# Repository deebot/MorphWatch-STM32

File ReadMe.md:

# MorphWatch-STM32

# Description
Morph watch is a wearable made for makers and hackers who want to do more with  their devices and want to have control over their data. As a normal functional device it shows time, date and no of steps,weather data . But it is more than that it can be used to run machine learning algorithums on 6 Axis IMU MPU6050 data to detect gestures. The small form factor and integrated battery also allows the user to attach the watch to a target lets say attach it to your bicycle to gather the vibration data, or attach it to a machine to gather the vibration data to  train a model for predicting breakdown and service durations. The device also  provides I2C interface to attach more sensorS as modules. It also provides interface  to connect with  STLINK-V2 and supports full debugging features using breakpoints and print statements. The watch is intended to have 2 Modes:

- Ultra Low Power Mode : In this mode the L476RG controller  wakes up ever 1 minute to update the minutes and then sleeps. The 2 buttons are configures as external intruppts and can be pressed to wake up the controller and do other tasks like going though the Menu and getting the status of external senors or IMU data. This mode should give very long battery life

- Normal Mode: In this mode the microcontroller is active all the time and can count steps and perform machine learning algorithums.

## <u>Features supported by Hardware</u>
Morph Watch has STM32-L476RG at its heart which has 128KB SRAM and 1MB Flash suitable for running Edge AI models. It has internal RTC and DFU support which allows updating the firmware over USB without any external USB to Serial convertor or Programmer. The watch has 2 buttons to navigate menu or work as external interrupts. The battary can be charegd using the onboard charging IC.The battery status can be monitored and diplayed on the Eink display. A 9 Axis IMU is onboard which allows user to create innovative projects. A vibration moter can be connected to get vibration feedback. A Bluetooth module JDY08 based on TI's CC2541 Chip allows user to connect to Android device over bluetooth 4.0. Diagram Below shoews the board and placement of  key components.

## <u>Schematic</u>

## <u>Uploading Code and Debugging</u>
Uploading the code is possible though USB in DFU mode by connecting the Boot Pin to HIGH  by either connecting the jumper using external wire or by shorting the jumper JP1 by soldering. To exit the DFU mode remove the jumper JP1 and powercycle. The code can also be uploaded using the Serial Wire debug interface. STlink Debugger/Programmer is need to use this interface.

## TO DO list

### Phase 1:

- [ ] Implement code to interface EINK Display using SPI protocol and control partial and complete refresh
- [ ] Implement code to interface IMU using I2C protocol and grab the raw data.
- [ ] Understanding the internal RTC functionality of L476RG and implementing code to get time and data.
- [ ] Understanding intruppts on L476RG and configuring buttons as external intruppts
- [ ] Implementing code to control the vibration motor

### Phase 2:

- [ ] Creating Menus on the Eink Display and switching between menu using buttons.
- [ ] Recognising Gestures using IMU and exploring Kalman filter 
- [ ] Understanding CRC hardware on board and implementing code to grab data. This functionality will be used to send CRC along with data to detect tempering
- [ ] Figure out a Generic app to check the functionality
- [ ] Integration of all the features to achieve functional Watch

### Phase 3:

- [ ] Understanding the Bluetooth4.0 and Write code to interface Bluetooth in transparent mode using UART
- [ ] Integration of Bluetooth functionality with other features
- [ ] Using  Bosch'S BlechC using STM HAL code.
- [ ] Exploring Low power modes of L476RG

## Story Behind : 
### A little story telling:

  Morph watch is inpired by [Watchy|SQFMI ](https://www.crowdsupply.com/sqfmi/watchy) which you can also back on crowdsource as on today 1Feb2021. For a long time i wanted to build my own smart watch which is hackable. My idea was to have a development board which is also a product in itself with certain concrete functionality and that is why i narrowed down on having a watch because i can have it on me as a watch but it can also be something else, a learning tool and its functionality can be extended by adding mods to it. 
### Why I chose what i chose
  I chose to build Morph Watch on STM32 L476RG which is based on ARM cortex M4. I have  some sort of romatisim for ARM architecture and  its not long since i have shifted from 8 bit segment to more capable 32 bit controllers which i often see in tear down of professional products, infact the Pebble watch was based on a STM32 microntroller and TI's bluetooth chip. Also because i had a nucleo board and already had a JDY08 module to write software. Further this STM variaent is quite capable of running AI algos and also also supports various low power modes. Further with  the STM line  it would be very easy to incorporate wirless line like STM32wb to add different wifi technologies to this watch. While ESP32 with Arduino IDE are very easy to use but I now prefer more serious debugging techniques using Debugger and breakpoints which is supported on this board.
  Also read  [MORPH watch Hackaday ](https://hackaday.io/project/177315-morph-watch)

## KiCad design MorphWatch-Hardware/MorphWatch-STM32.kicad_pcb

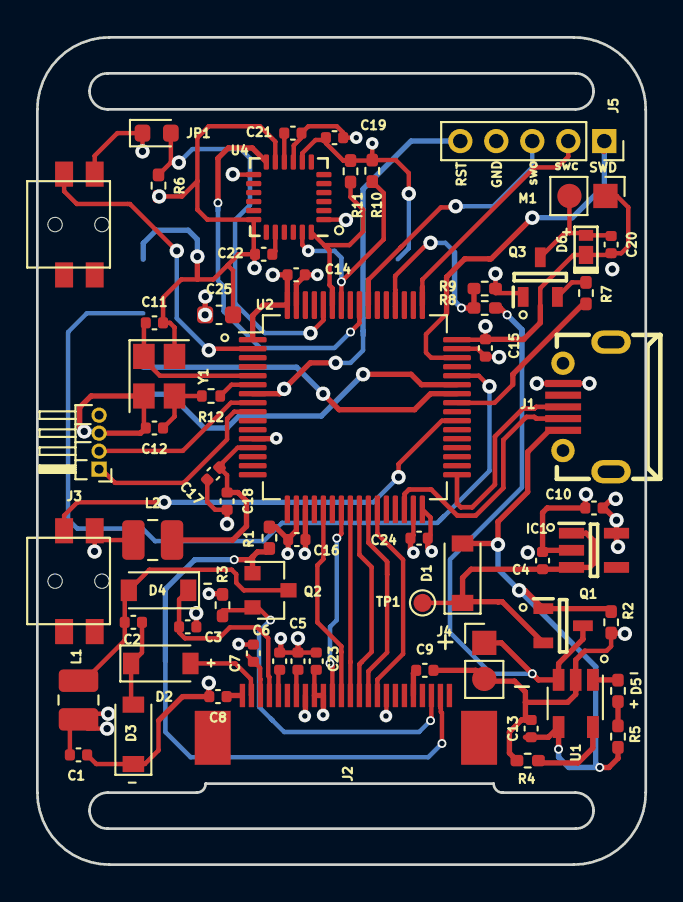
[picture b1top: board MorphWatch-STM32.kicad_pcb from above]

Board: 4 copper layers, 33.8 x 46.0 mm, 64 parts (1 on the bottom side), 52 nets.

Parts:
C1: 4.7uF/50v; C_0402_1005Metric
C2, C10: 4.7uf/50v; C_0402_1005Metric
C3, C5, C6, C7, C8, C9, C23: 1uf/50v; C_0402_1005Metric
C4, C13: 1uf; C_0402_1005Metric
C11, C12, C14, C15, C16, C17, C18, C19, C20, C21, C22, C24: C; C_0402_1005Metric
C25: 4.7uf; C_0603_1608Metric
D1, D2, D3, D4: MBR0530; D_SOD-123
D5: LED; R_0402_1005Metric_Pad0.72x0.64mm_HandSolder
D6: Diode; U-DFN1608-2_L1.6-W0.8-RD
IC1: ME6211C33M5G-N; SOT95P270X145-5N
J1: USB; MICRO-USB-SMD_MICROXNJ
J2: Conn_01x24; 24_Pins_0.5mm_Pitch_ZIF_Connector_UP
J3: Conn_01x04; PinHeader_1x04_P1.00mm_Horizontal
J4: Conn_01x02; Motor_Header
J5: Conn_01x05; PinSocket_1x05_P2.00mm_Vertical
JP1: SolderJumper_2_Open; D_0603_1608Metric
L1: 27uH; L_1008_2520Metric
L2: 27n; L_1008_2520Metric
M1: Motor_DC_ALT; Motor_Header
Q1: CJ2301_S1; SOT95P240X115-3N
Q2: DMN3042L; SOT-23
Q3: S8050; SOT95P240X115-3N
R1, R2, R4: 10k; R_0402_1005Metric_Pad0.72x0.64mm_HandSolder
R3: 3; R_0402_1005Metric_Pad0.72x0.64mm_HandSolder
R5: 1k; R_0402_1005Metric_Pad0.72x0.64mm_HandSolder
R6, R7, R8, R9: R; R_0402_1005Metric_Pad0.72x0.64mm_HandSolder
R10, R11: 2.2k; R_0402_1005Metric_Pad0.72x0.64mm_HandSolder
R12: 5; R_0402_1005Metric
S1, S2: GPTS203211B; K2-1114SA-A4SW-06
TP1: TestPoint; TestPoint_Pad_D1.0mm
U1: TP4054; TSOT-23-5
U2: STM32L476RGTx; LQFP-64_10x10mm_P0.5mm
U3: JDY-08; JDY-08_HandSoldering
U4: MPU-6050; InvenSense_QFN-24_4x4mm_P0.5mm
Y1: Crystal_GND24; Crystal_SMD_3225-4Pin_3.2x2.5mm

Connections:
+3.3VA: C17.1, C18.1, L2.2, U2.13
+3V3: C1.1, C10.1, C14.1, C15.1, C16.1, C19.1, C20.1, C23.2, C24.1, C25.1, D6.1, IC1.5, J2.15, J2.16, J3.4, JP1.1, L1.1, L2.1, M1.1, R10.2, R11.2, S1.2, S2.2, U2.1, U2.19, U2.32, U2.48, U2.64, U3.1, U4.8, U4.13
+BATT: J4.1, Q1.3, R8.1, U1.3
BATT_STAT: R8.2, R9.1, U2.52
BUSY: J2.9, U2.27
BUT1: S1.1, U2.39
BUT2: S2.1, U2.2
DC: J2.11, U2.25
EXTSENSCL: J3.2, U2.8
EXTSENSDA: J3.1, U2.9
GDR: J2.2, Q2.1, R1.2
GND: C1.2, C3.2, C4.2, C5.2, C6.2, C7.2, C8.2, C9.2, C10.2, C11.2, C12.2, C13.1, C14.2, C15.2, C16.2, C17.2, C18.2, C19.2, C21.2, C22.2, C23.1, C24.2, C25.2, D3.1, IC1.2, J1.5, J2.8, J2.17, J3.3, J4.2, J5.4, Q3.1, R1.1, R2.1, R3.1, R4.2, R6.2, R9.2, U1.2, U2.12, U2.18, U2.31, U2.47, U2.63, U3.24, U4.1, U4.9, U4.11, U4.18, Y1.2, Y1.4
INT: U2.56, U4.12
MOSI: J2.14, U2.23
NRST: J5.5, U2.7
unnamed: C2.1, D2.1, D3.2
unnamed: C2.2, D4.2, L1.2, Q2.3
unnamed: C4.1, D1.1, IC1.1, IC1.3, Q1.2, TP1.1
unnamed: C5.1, J2.18
unnamed: C6.1, J2.20
unnamed: C7.1, J2.22
unnamed: C8.1, J2.24
unnamed: C9.1, J2.5
unnamed: C11.1, U2.5, Y1.1
unnamed: C12.1, R12.2, Y1.3
unnamed: C20.2, D6.2, M1.2, Q3.3
unnamed: C21.1, U4.10
unnamed: C22.1, U4.20
unnamed: D5.1, U1.1
unnamed: D5.2, R5.2
unnamed: JP1.2, R6.1, U2.60
unnamed: Q3.2, R7.1
unnamed: R4.1, U1.5
unnamed: R12.1, U2.6
PREVGH: C3.1, D4.1, J2.21
PREVGL: D2.2, J2.23
RES: J2.10, U2.26
RESE: J2.3, Q2.2, R3.2
RXD: U2.42, U3.20
SCK: J2.13, U2.21
SS: J2.12, U2.24
SWCLK: J5.2, U2.49
TXD: U2.43, U3.19
TraceSWO: J5.3, U2.55
USB_B+: J1.3, U2.33
USB_B-: J1.2, U2.30
VBUS: C13.2, D1.2, J1.1, Q1.1, R2.2, R5.1, U1.4
VIB_MOT: R7.2, U2.41
Wakeup: U2.44, U3.22
imuSCL: R10.1, U2.58, U4.23
imuSDA: R11.1, U2.59, U4.24
swdebug: J5.1, U2.46

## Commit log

2021-02-02 Added Schematic,BoardFile and associated files
2021-02-02 Added Readme File
2021-02-03 Added Images
2021-02-03 Added information about features, uploading code and displayed images
2021-02-04 Made changes to satisfy DRC
2021-02-04 Added Gerber files and Pick & Place file
2021-02-04 Added tasks in the todo list
2021-02-04 Modified the Board to funlfil DRC rules
2021-02-05 Updated Board to satisfy DRC
2021-02-05 Added Link to Hackaday
